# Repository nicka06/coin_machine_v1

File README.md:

# coin_machine_v1

This is an automated coin machine, allowing an individual to easily take pictures of all the coins that they have. It works very simply. The user inserts the coin into the chute located at the front of the machine. Once the coin has made its way to the flipper, the servo flips it over twice, allowing the camera to take a picture of both sides. Following the completion of the flips, the coin is ejected, taking it through external coin chute and collection box. Beyond the mechanics of the camera/flipper system, the system has an additional chute that is opened by the servo connected to the excursion on the right side of the mahine. If the system recognizes multiple coins in the system (via the phototransistor sensor), the chute will open up, removing the extra coins from the system via the second external coin chute. This coin chute brings the extra coins to the front of the machine.

I'm building this automated coin machine due to my love of coins. I enjoy collecting them and taking pictures of the new ones I get at the bank to keep track of them. As you can imagine, this is an extremely difficult and annoying process. This cuts through all of it, making the grueling process much better. Later, I'll also be able to add more features such as automatic value estimator and more. I can't wait to finish building it!

|Item                |Link                                                                                                                                                                                                                                                                                                                                                                                                                                                                                                                                                                                                                                                                                                                                                                                                                                                                                                |Step/STL File                                                                                                                                                                                                                                                    |Price (bf tax + ship)|Quantity|Total |
|--------------------|----------------------------------------------------------------------------------------------------------------------------------------------------------------------------------------------------------------------------------------------------------------------------------------------------------------------------------------------------------------------------------------------------------------------------------------------------------------------------------------------------------------------------------------------------------------------------------------------------------------------------------------------------------------------------------------------------------------------------------------------------------------------------------------------------------------------------------------------------------------------------------------------------|-----------------------------------------------------------------------------------------------------------------------------------------------------------------------------------------------------------------------------------------------------------------|---------------------|--------|------|
|Microcontroller     |https://www.digikey.com/en/products/detail/espressif-systems/ESP32-DEVKITC-32E/12091810?gQT=2                                                                                                                                                                                                                                                                                                                                                                                                                                                                                                                                                                                                                                                                                                                                                                                                       |N/A                                                                                                                                                                                                                                                              |8.09                 |1       |16.18 |
|Battery Holder      |https://www.digikey.com/en/products/detail/olimex-ltd/BAT-HOLDER-4XAA/21662650?gad_source=1&gad_campaignid=20783325532&gbraid=0AAAAADrbLliVhFDAqSriuXbsC1EiN0tFu&gclid=CjwKCAjw7fzDBhA7EiwAOqJkh9lExZeceX_pAcL-1aVytfFR7L3JOBg_X3Y_iLB_qMWwFW642HeTPBoCh-kQAvD_BwE&gclsrc=aw.ds                                                                                                                                                                                                                                                                                                                                                                                                                                                                                                                                                                                                                     |DNE                                                                                                                                                                                                                                                              |0.59                 |1       |1.18  |
|Servos              |https://www.amazon.com/Miuzei-Geared-Helicopter-Arduino-Project/dp/B0CP98TZJ2/ref=asc_df_B0BWJ2CK9D?mcid=42fb0e1405373275a8e090bd2b714df8&hvocijid=4752185336220157426-B0BWJ2CK9D-&hvexpln=73&tag=hyprod-20&linkCode=df0&hvadid=721245378154&hvpos=&hvnetw=g&hvrand=4752185336220157426&hvpone=&hvptwo=&hvqmt=&hvdev=c&hvdvcmdl=&hvlocint=&hvlocphy=9017274&hvtargid=pla-2281435178618&th=1                                                                                                                                                                                                                                                                                                                                                                                                                                                                                                         |https://www.electronicoscaldas.com/datasheet/MG90S_Tower-Pro.pdf?srsltid=AfmBOopFh5ZP-KCsfEakkL5yVIUkPUQWl2_Do_A8-68RYsNCWP2CnjHr                                                                                                                                |13.99                |0.5     |13.99 |
|Sensor              |https://www.digikey.com/en/products/detail/lite-on-inc/LTH-301-05/3198344?gad_source=1&gad_campaignid=21273973101&gbraid=0AAAAADrbLljyWGOCHlFFcfZETCdLezsJF&gclid=CjwKCAjw7fzDBhA7EiwAOqJkh-4MRv9nci754U5Sh_1Gk9tgjCk57-jxSNfryezqVYfAlnWVnRdQyhoCRuMQAvD_BwE&gclsrc=aw.ds                                                                                                                                                                                                                                                                                                                                                                                                                                                                                                                                                                                                                          |https://optoelectronics.liteon.com/upload/download/DS-55-92-0002/H301-05.pdf                                                                                                                                                                                     |0.7                  |1       |1.4   |
|Light indicator     |https://www.digikey.com/en/products/detail/inolux/HV-5RGB60/7604616?gad_source=1&gad_campaignid=20228387720&gbraid=0AAAAADrbLlilqazAoxr5q6IYaw-_-vecu&gclid=CjwKCAjw7fzDBhA7EiwAOqJkh5ecru-l1ZT5LI9ApcwNIsJfQR3MiCSApFQpVOKJvI3g9hOXdcG7nxoCkHAQAvD_BwE&gclsrc=aw.ds                                                                                                                                                                                                                                                                                                                                                                                                                                                                                                                                                                                                                                |https://www.inolux-corp.com/datasheet/Inolux%20Lamp/TH%20Lamp/HV-5RGBXX%205mm%20Full-Color%20Series.pdf                                                                                                                                                          |1.06                 |1       |2.12  |
|Camera              |https://www.alibaba.com/product-detail/p_62408774762.html?mark=google_shopping&src=sem_ggl&field=UG&from=sem_ggl&cmpgn=22635874527&adgrp=177485315221&fditm=&tgt=pla-2412849993011&locintrst=&locphyscl=9017274&mtchtyp=&ntwrk=g&device=c&dvcmdl=&creative=756472634791&plcmnt=&plcmntcat=&aceid=&position=&gad_source=1&gad_campaignid=22635874527&gbraid=0AAAAAD8m77qg6GjXGnNFPJJNBO7JP-gd_&gclid=CjwKCAjw7fzDBhA7EiwAOqJkh3sFHvHTk25Bfiihhjd1lV5CSma3N9T0DB5zS5NlOl8mMyo-YxnT0xoCuTgQAvD_BwE                                                                                                                                                                                                                                                                                                                                                                                                     |https://us-icbuim-file.oss-us-east-1.aliyuncs.com/chat/bdf5eb8cdbcff22f275396a9d335c13d.pdf?Expires=1753401367&OSSAccessKeyId=LTAIxlzvmECyZvmX&Signature=MnHNZHGWvgjN2qB4v0weXyZ1VoA%3D&response-content-disposition=filename%3DOV2640-camera%20module%281%29.pdf|1.92                 |1       |3.84  |
|Camera lights       |https://www.amazon.com/BTF-LIGHTING-WS2812B1M60LB30-BTF-LIGHTING-WS2812B-IC-RGB-5050SMD-Pure-Gold-Individual-Addressable-LED-Strip-High-Quality-3-28FT-60LED-60LED-m-Flexible-Full-Color-IP30-DC5V-for-DIY-Chasing-Color-Project-No-Adapter-or-Controller/dp/B01CDTED80/ref=asc_df_B01CDTED80?mcid=aab6f3a36a97389abee1397380f9f389&hvocijid=12922171453011528359-B01CDTED80-&hvexpln=73&tag=hyprod-20&linkCode=df0&hvadid=721245378154&hvpos=&hvnetw=g&hvrand=12922171453011528359&hvpone=&hvptwo=&hvqmt=&hvdev=c&hvdvcmdl=&hvlocint=&hvlocphy=9017274&hvtargid=pla-2281435178138&th=1                                                                                                                                                                                                                                                                                                             |DNE                                                                                                                                                                                                                                                              |8.99                 |0.5     |8.99  |
|buck converter      |https://www.alibaba.com/product-detail/p_1601286665356.html?mark=google_shopping&src=sem_ggl&field=UG&from=sem_ggl&cmpgn=22635874527&adgrp=177485315221&fditm=&tgt=pla-2412849993011&locintrst=&locphyscl=9017274&mtchtyp=&ntwrk=g&device=c&dvcmdl=&creative=756472634791&plcmnt=&plcmntcat=&aceid=&position=&gad_source=1&gad_campaignid=22635874527&gbraid=0AAAAAD8m77qg6GjXGnNFPJJNBO7JP-gd_&gclid=CjwKCAjw7fzDBhA7EiwAOqJkh8IpI8KVBmbsfgQdDGbDhzUhFWClT8oR7es3Ld-Gnn2vdX73xH4lPhoCQGAQAvD_BwE                                                                                                                                                                                                                                                                                                                                                                                                   |DNE                                                                                                                                                                                                                                                              |0.38                 |1       |0.76  |
|1000Uf Capacitor    |https://www.digikey.com/en/products/detail/nichicon/UCM1C102MNL1GS/4991837                                                                                                                                                                                                                                                                                                                                                                                                                                                                                                                                                                                                                                                                                                                                                                                                                          |N/A                                                                                                                                                                                                                                                              |1.03                 |1       |2.06  |
|indicator resistor  |https://www.digikey.com/en/products/detail/yageo/RC0805FR-10220RL/14008826?gad_source=1&gad_campaignid=17335707486&gbraid=0AAAAADrbLlhVc93_s6E8uaIuN5tZzR-_j&gclid=CjwKCAjw7fzDBhA7EiwAOqJkh527CsFJCFbNzJa69-usU-6znfyDCfmTJSqq4D7XPAFFFQfJqj3mFBoC7a4QAvD_BwE&gclsrc=aw.ds                                                                                                                                                                                                                                                                                                                                                                                                                                                                                                                                                                                                                         |N/A                                                                                                                                                                                                                                                              |0.1                  |1       |0.2   |
|ligihting resistor  |https://www.digikey.com/en/products/detail/yageo/RC0805FR-13470RL/14287677?gad_source=1&gad_campaignid=17335707486&gbraid=0AAAAADrbLlhVc93_s6E8uaIuN5tZzR-_j&gclid=CjwKCAjw7fzDBhA7EiwAOqJkh6SjgU5tvYCDcH23XbF9Sm-n1YFcr90ZDsH0mtF9SQlWFqA2rrIOJBoCB7sQAvD_BwE&gclsrc=aw.ds                                                                                                                                                                                                                                                                                                                                                                                                                                                                                                                                                                                                                         |N/A                                                                                                                                                                                                                                                              |0.1                  |3       |0.6   |
|Power Connector     |https://www.digikey.com/en/products/detail/w-rth-elektronik/691137710002/6644051?gad_source=1&gad_campaignid=20783325532&gbraid=0AAAAADrbLliVhFDAqSriuXbsC1EiN0tFu&gclid=CjwKCAjw7fzDBhA7EiwAOqJkh-Bb2QKet9_pYhijm2KMMvVEnmYei8YaacJxVmhynZg-Uwv72SVy0hoCbP0QAvD_BwE&gclsrc=aw.ds                                                                                                                                                                                                                                                                                                                                                                                                                                                                                                                                                                                                                   |N/A                                                                                                                                                                                                                                                              |0.74                 |1       |1.48  |
|Servo connector     |https://www.digikey.com/en/products/detail/w-rth-elektronik/61300311121/4846825?gad_source=1&gad_campaignid=20783325532&gbraid=0AAAAADrbLliVhFDAqSriuXbsC1EiN0tFu&gclid=CjwKCAjw7fzDBhA7EiwAOqJkh7k0ZqGigQ8fIXtJe9X_ndHCoqhIOY7n4aBzgHr9SU1ySnTK-kh5cBoC0dIQAvD_BwE&gclsrc=aw.ds                                                                                                                                                                                                                                                                                                                                                                                                                                                                                                                                                                                                                    |N/A                                                                                                                                                                                                                                                              |0.12                 |2       |0.48  |
|Sensor board male   |https://www.digikey.com/en/products/detail/jst-sales-america-inc/B4B-XH-A/1651047                                                                                                                                                                                                                                                                                                                                                                                                                                                                                                                                                                                                                                                                                                                                                                                                                   |N/A                                                                                                                                                                                                                                                              |0.14                 |1       |0.28  |
|Sensor female       |https://www.digikey.com/en/products/detail/jst-sales-america-inc/XHP-4/683353?gad_source=1&gad_campaignid=20783325532&gbraid=0AAAAADrbLliVhFDAqSriuXbsC1EiN0tFu&gclid=CjwKCAjw7fzDBhA7EiwAOqJkh9NHV0fgVVolWw4eS8IlJ5sSFwxfHwGC5bGIJy-NbtyIyNqZi9RRExoCljAQAvD_BwE&gclsrc=aw.ds                                                                                                                                                                                                                                                                                                                                                                                                                                                                                                                                                                                                                      |N/A                                                                                                                                                                                                                                                              |0.1                  |1       |0.2   |
|Sensor Connector    |https://www.digikey.com/en/products/detail/jst-sales-america-inc/ASXHSXH22K254/9961919?gad_source=1&gad_campaignid=20783325532&gbraid=0AAAAADrbLliVhFDAqSriuXbsC1EiN0tFu&gclid=CjwKCAjw7fzDBhA7EiwAOqJkh5DnN7jklYFYkHG5uHZpRNlbtVd7Oir44CJWwkA4VteMcgy3hPduHxoCmasQAvD_BwE&gclsrc=aw.ds                                                                                                                                                                                                                                                                                                                                                                                                                                                                                                                                                                                                             |N/A                                                                                                                                                                                                                                                              |0.77                 |4       |6.16  |
|Indicator board male|https://www.digikey.com/en/products/detail/jst-sales-america-inc/B4B-XH-A/1651047                                                                                                                                                                                                                                                                                                                                                                                                                                                                                                                                                                                                                                                                                                                                                                                                                   |N/A                                                                                                                                                                                                                                                              |0.14                 |1       |0.28  |
|Indicator Female    |https://www.digikey.com/en/products/detail/jst-sales-america-inc/XHP-4/683353?gad_source=1&gad_campaignid=20783325532&gbraid=0AAAAADrbLliVhFDAqSriuXbsC1EiN0tFu&gclid=CjwKCAjw7fzDBhA7EiwAOqJkh9NHV0fgVVolWw4eS8IlJ5sSFwxfHwGC5bGIJy-NbtyIyNqZi9RRExoCljAQAvD_BwE&gclsrc=aw.ds                                                                                                                                                                                                                                                                                                                                                                                                                                                                                                                                                                                                                      |N/A                                                                                                                                                                                                                                                              |0.1                  |1       |0.2   |
|Indicator Connector |https://www.digikey.com/en/products/detail/jst-sales-america-inc/ASXHSXH22K254/9961919?gad_source=1&gad_campaignid=20783325532&gbraid=0AAAAADrbLliVhFDAqSriuXbsC1EiN0tFu&gclid=CjwKCAjw7fzDBhA7EiwAOqJkh5DnN7jklYFYkHG5uHZpRNlbtVd7Oir44CJWwkA4VteMcgy3hPduHxoCmasQAvD_BwE&gclsrc=aw.ds                                                                                                                                                                                                                                                                                                                                                                                                                                                                                                                                                                                                             |N/A                                                                                                                                                                                                                                                              |0.77                 |4       |6.16  |
|Lightning Board Male|https://www.digikey.com/en/products/detail/jst-sales-america-inc/B3B-XH-A/1651046?gQT=2                                                                                                                                                                                                                                                                                                                                                                                                                                                                                                                                                                                                                                                                                                                                                                                                             |N/A                                                                                                                                                                                                                                                              |0.11                 |1       |0.22  |
|Lightning Female    |https://www.digikey.com/en/products/detail/jst-sales-america-inc/XHP-3/1651017?gad_source=1&gad_campaignid=20783325532&gbraid=0AAAAADrbLliVhFDAqSriuXbsC1EiN0tFu&gclid=CjwKCAjw7fzDBhA7EiwAOqJkh0szjal3su0_NWrAzNAr5G-FByRr-OJ676SJIIHM14zMB8CPOGMTzxoCA6UQAvD_BwE&gclsrc=aw.ds                                                                                                                                                                                                                                                                                                                                                                                                                                                                                                                                                                                                                     |N/A                                                                                                                                                                                                                                                              |0.1                  |1       |0.2   |
|Lightning Connector |https://www.digikey.com/en/products/detail/jst-sales-america-inc/ASXHSXH22K102/9961917?gad_source=1&gad_campaignid=20783325532&gbraid=0AAAAADrbLliVhFDAqSriuXbsC1EiN0tFu&gclid=CjwKCAjw7fzDBhA7EiwAOqJkhzK51Ulog5UlvsnLFx2dJwa5w1kF-NlyuTQiaTBXq1XXI8Fw2hAuwhoCB_AQAvD_BwE&gclsrc=aw.ds                                                                                                                                                                                                                                                                                                                                                                                                                                                                                                                                                                                                             |N/A                                                                                                                                                                                                                                                              |0.71                 |3       |4.26  |
|Camera Connector    |https://www.digikey.com/en/products/detail/gct/FFC2B35-24-T/15970899?gad_source=1&gad_campaignid=20783325532&gbraid=0AAAAADrbLliVhFDAqSriuXbsC1EiN0tFu&gclid=CjwKCAjw7fzDBhA7EiwAOqJkh5T_thEZS1M6HrS-AfnBT7NRnk53y2lwZdgMWC0IgW4F0ARWhsPKfxoCWAgQAvD_BwE&gclsrc=aw.ds                                                                                                                                                                                                                                                                                                                                                                                                                                                                                                                                                                                                                               |N/A                                                                                                                                                                                                                                                              |0.44                 |1       |0.88  |
|Camera Wire         |https://www.digikey.com/en/products/detail/gct/05-24-D-0101-A-4-06-4-T/21266768?gad_source=1&gad_campaignid=20783325532&gbraid=0AAAAADrbLliVhFDAqSriuXbsC1EiN0tFu&gclid=CjwKCAjw7fzDBhA7EiwAOqJkhzU6E8l8bZqvpxGzcDuJ6DBf5WbZ8UexZIeN3UTRr_NjPMQn-uATjxoCW9sQAvD_BwE&gclsrc=aw.ds                                                                                                                                                                                                                                                                                                                                                                                                                                                                                                                                                                                                                    |N/A                                                                                                                                                                                                                                                              |1.29                 |1       |2.58  |
|Regular wire        |https://www.amazon.com/Fermerry-Stranded-Electrical-Silicone-Cables/dp/B089CHVN7G?source=ps-sl-shoppingads-lpcontext&ref_=fplfs&gQT=0&th=1                                                                                                                                                                                                                                                                                                                                                                                                                                                                                                                                                                                                                                                                                                                                                          |N/A                                                                                                                                                                                                                                                              |9.99                 |0.5     |9.99  |
|Foam for pcb        |https://www.aliexpress.us/item/3256805442378894.html?src=google&pdp_npi=4%40dis%21USD%212.22%212.22%21%21%21%21%21%40%2112000033806745946%21ppc%21%21%21&src=google&albch=shopping&acnt=708-803-3821&isdl=y&slnk=&plac=&mtctp=&albbt=Google_7_shopping&aff_platform=google&aff_short_key=UneMJZVf&gclsrc=aw.ds&albagn=888888&ds_e_adid=&ds_e_matchtype=&ds_e_device=c&ds_e_network=x&ds_e_product_group_id=&ds_e_product_id=en3256805442378894&ds_e_product_merchant_id=550323114&ds_e_product_country=US&ds_e_product_language=en&ds_e_product_channel=online&ds_e_product_store_id=&ds_url_v=2&albcp=19678427463&albag=&isSmbAutoCall=false&needSmbHouyi=false&gad_source=1&gad_campaignid=19686402437&gbraid=0AAAAAD6I-hHbTWnjWfXa3b0JiSIiDnXs9&gclid=Cj0KCQjwnJfEBhCzARIsAIMtfKLkC6tFrY03lzOqCGZFSbhi-ocjRXtpVGObKZPs3HCTurApQOjS8mcaApdxEALw_wcB&gatewayAdapt=glo2usa                          |N/A                                                                                                                                                                                                                                                              |6.58                 |0.5     |6.58  |
|Screws              |https://www.homedepot.com/p/Everbilt-M3-0-5-x-10-mm-Plain-Metric-Socket-Cap-Screw-3-Piece-per-Bag-803188/204808024?g_store=2728&source=shoppingads&locale=en-US&gStoreCode=2728&gQT=1                                                                                                                                                                                                                                                                                                                                                                                                                                                                                                                                                                                                                                                                                                               |N/A                                                                                                                                                                                                                                                              |2.25                 |2       |9     |
|More Screws         |https://www.homedepot.com/p/Prime-Line-M2-0-4-x-20-mm-Black-Oxide-Coated-Steel-Class-12-9-Metric-Internal-Hex-Socket-Head-Set-Screws-10-Pack-9180136/311732337                                                                                                                                                                                                                                                                                                                                                                                                                                                                                                                                                                                                                                                                                                                                      |N/A                                                                                                                                                                                                                                                              |4.99                 |0.5     |4.99  |
|Magnets             |https://www.aliexpress.us/item/3256807909032358.html?src=google&pdp_npi=4%40dis%21USD%217.18%214.06%21%21%21%21%21%40%2112000043701895592%21ppc%21%21%21&snpsid=1&snps=y&snpsid=1&src=google&albch=shopping&acnt=742-864-1166&isdl=y&slnk=&plac=&mtctp=&albbt=Google_7_shopping&aff_platform=google&aff_short_key=_oDeeeiG&gclsrc=aw.ds&albagn=888888&ds_e_adid=&ds_e_matchtype=&ds_e_device=c&ds_e_network=x&ds_e_product_group_id=&ds_e_product_id=en3256807909032358&ds_e_product_merchant_id=5551326180&ds_e_product_country=US&ds_e_product_language=en&ds_e_product_channel=online&ds_e_product_store_id=&ds_url_v=2&albcp=22443129574&albag=&isSmbAutoCall=false&needSmbHouyi=false&gad_source=1&gad_campaignid=22443130765&gbraid=0AAAAA99aYpd2U62zy7NJbxugve-htRI8R&gclid=Cj0KCQjw-ZHEBhCxARIsAGGN96LJc0CtVUfNG208x3nD6uTlhOKRtQ0U2k0tnoKhLppi9lUUB-NWHHAaAvCEEALw_wcB&gatewayAdapt=glo2usa|N/A                                                                                                                                                                                                                                                              |0.99                 |1       |1.98  |
|filament            |https://www.amazon.com/eSUN-Filament-Printing-Printer-Designed/dp/B0DGQBMJMK/ref=sr_1_16?dib=eyJ2IjoiMSJ9.Razt1k5uVOV2TzDUjSQvl7XEcxdtlHmAdZQWosMeTQ50CwFn7o1y91poBYqmVyD9HxIA_A0r02FOmVlrp1nPMesRN62hAAydwv-PxE5Qi07-Ww0ryQYsGgAqZsrmEU20zU0_ffjW8d8uhPSc8SdO0CSTQG0t-tMYp2xMcieXr8z_RaTrzCr2jQG8r_7wSBk8uNSQbhB2PLppIrgodCKK9YNonEEP75L9N3QZLqYCnD0.fJtDJZ7egESpQDcGEz5eu_KVAuM1CXnrID5a33sKsjs&dib_tag=se&hvadid=695206731837&hvdev=c&hvexpln=67&hvlocphy=9190255&hvnetw=g&hvocijid=9219964727381373825--&hvqmt=e&hvrand=9219964727381373825&hvtargid=kwd-320787596539&hydadcr=8497_13654088&keywords=pla%2Bamazon&mcid=987f97c45f7b3a3dac93ebf26610d89d&qid=1754454039&sr=8-16&th=1                                                                                                                                                                                                             |N/A                                                                                                                                                                                                                                                              |13.39                |0.5     |13.39 |
|pcb                 |N/A                                                                                                                                                                                                                                                                                                                                                                                                                                                                                                                                                                                                                                                                                                                                                                                                                                                                                                 |N/A                                                                                                                                                                                                                                                              |2                    |0.5     |2     |
|Shipping + Tax      |                                                                                                                                                                                                                                                                                                                                                                                                                                                                                                                                                                                                                                                                                                                                                                                                                                                                                                    |                                                                                                                                                                                                                                                                 |                     |        |35    |
|                    |                                                                                                                                                                                                                                                                                                                                                                                                                                                                                                                                                                                                                                                                                                                                                                                                                                                                                                    |                                                                                                                                                                                                                                                                 |                     |        |157.63|
|                    |                                                                                                                                                                                                                                                                                                                                                                                                                                                                                                                                                                                                                                                                                                                                                                                                                                                                                                    |a                                                                                                                                                                                                                                                                |                     |        |      |

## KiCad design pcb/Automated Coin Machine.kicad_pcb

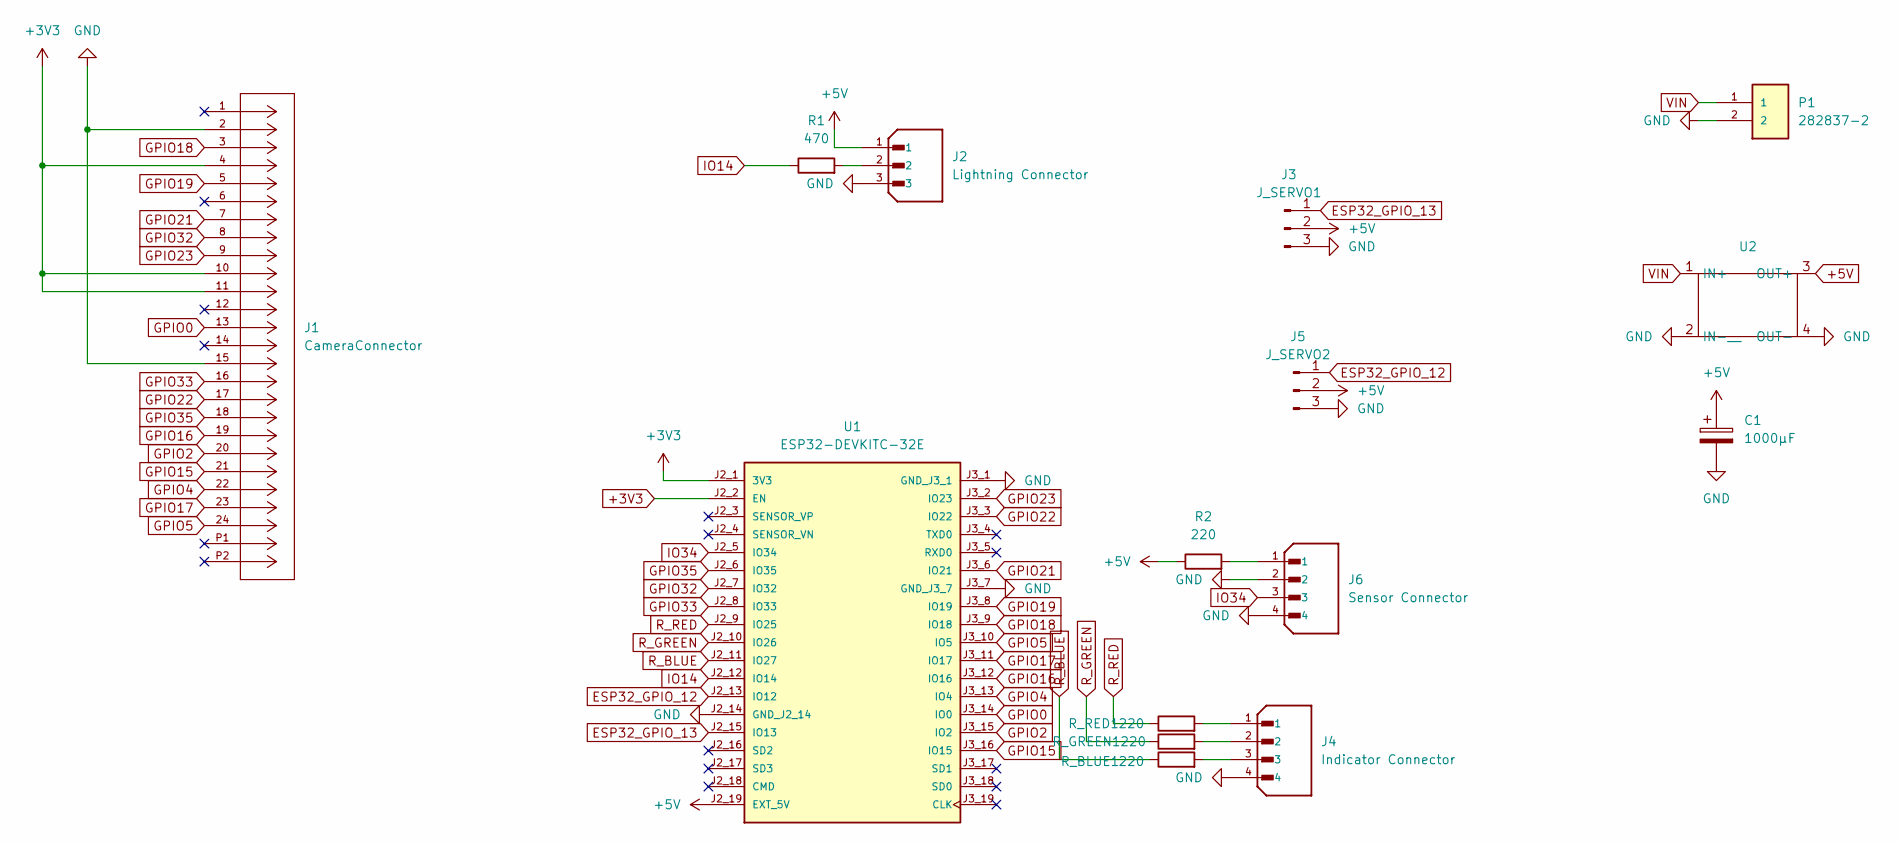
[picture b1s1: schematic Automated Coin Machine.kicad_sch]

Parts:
C1: 1000µF; 1000UFCapacitor
J1: CameraConnector; MANUFACTURER_PART_NUMBER 5051102491
J2: Lightning Connector; LightningConnector; PARTREV 7/4/21; DigiKey_Part_Number 455-2248-ND
J3: J_SERVO1; ServoConnector
J4: Indicator Connector; SensorIndicatorConnector; PARTREV 7/4/21; DigiKey_Part_Number 455-B4B-XH-A-ND
J5: J_SERVO2; ServoConnector
J6: Sensor Connector; SensorIndicatorConnector; PARTREV 7/4/21; DigiKey_Part_Number 455-B4B-XH-A-ND
P1: 282837-2; PowerConnector; PARTREV G3
R1: 470; LightningResistor
R2: 220; IndicatorResistor
R_BLUE1: 220; IndicatorResistor
R_GREEN1: 220; IndicatorResistor
R_RED1: 220; IndicatorResistor
U1: ESP32-DEVKITC-32E; ESP32; PARTREV 1.4
U2: LM2596_Module

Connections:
+3V3: J1.4, J1.10, J1.11, U1.J2_1 (3V3), U1.J2_2 (EN)
+5V: C1.1, J2.1, J3.2, J5.2, R2.1, U1.J2_19 (EXT_5V), U2.3 (OUT+)
ESP32_GPIO_12: J5.1, U1.J2_13 (IO12)
ESP32_GPIO_13: J3.1, U1.J2_15 (IO13)
GND: C1.2, J1.2, J1.15, J2.3, J3.3, J4.4, J5.3, J6.2, J6.4, P1.2, U1.J2_14 (GND_J2_14), U1.J3_1 (GND_J3_1), U1.J3_7 (GND_J3_7), U2.2 (IN-__), U2.4 (OUT-)
GPIO0: J1.13, U1.J3_14 (IO0)
GPIO2: J1.20, U1.J3_15 (IO2)
GPIO4: J1.22, U1.J3_13 (IO4)
GPIO5: J1.24, U1.J3_10 (IO5)
GPIO15: J1.21, U1.J3_16 (IO15)
GPIO16: J1.19, U1.J3_12 (IO16)
GPIO17: J1.23, U1.J3_11 (IO17)
GPIO18: J1.3, U1.J3_9 (IO18)
GPIO19: J1.5, U1.J3_8 (IO19)
GPIO21: J1.7, U1.J3_6 (IO21)
GPIO22: J1.17, U1.J3_3 (IO22)
GPIO23: J1.9, U1.J3_2 (IO23)
GPIO32: J1.8, U1.J2_7 (IO32)
GPIO33: J1.16, U1.J2_8 (IO33)
GPIO35: J1.18, U1.J2_6 (IO35)
IO14: R1.1, U1.J2_12 (IO14)
IO34: J6.3, U1.J2_5 (IO34)
unnamed: J2.2, R1.2
unnamed: J4.1, R_RED1.2
unnamed: J4.2, R_GREEN1.2
unnamed: J4.3, R_BLUE1.2
unnamed: J6.1, R2.2
R_BLUE: R_BLUE1.1, U1.J2_11 (IO27)
R_GREEN: R_GREEN1.1, U1.J2_10 (IO26)
R_RED: R_RED1.1, U1.J2_9 (IO25)
VIN: P1.1, U2.1 (IN+)

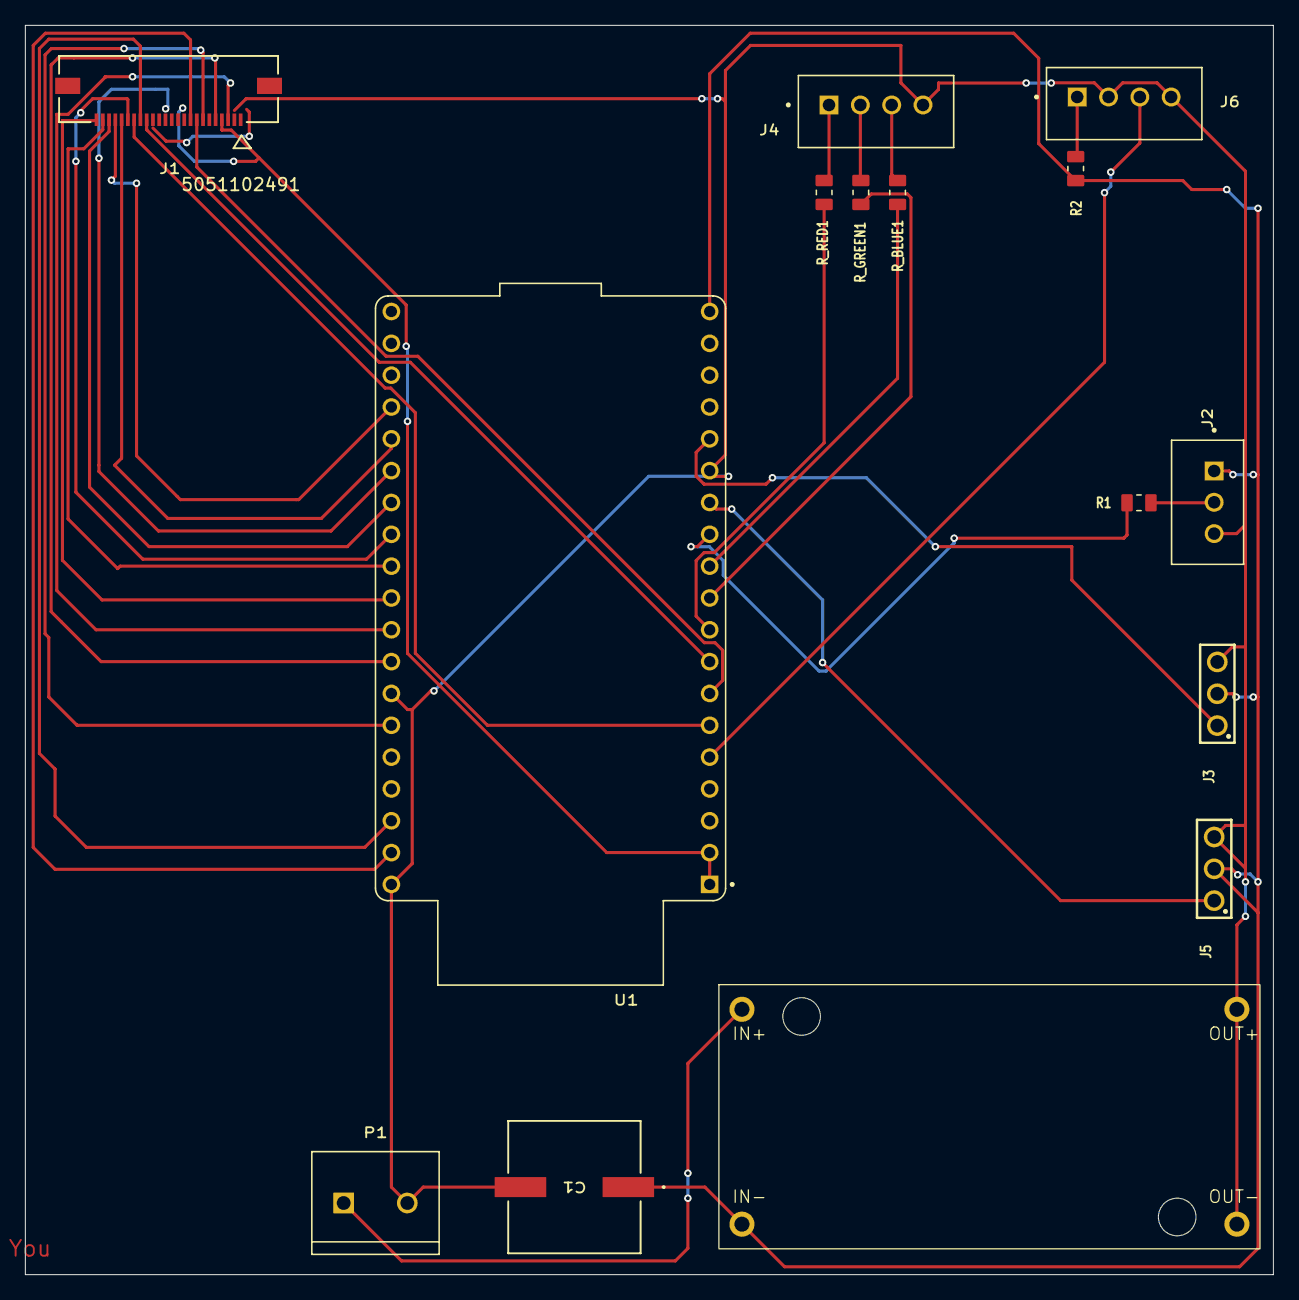
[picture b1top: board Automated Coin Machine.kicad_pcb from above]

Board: 2 copper layers, 99.6 x 99.7 mm, 15 parts (0 on the bottom side), 31 nets.

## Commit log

2025-07-26 Create bom
2025-07-26 Create Main
2025-07-27 firmware added
